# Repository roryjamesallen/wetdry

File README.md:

# wetdry
Wet/Dry control for Eurorack

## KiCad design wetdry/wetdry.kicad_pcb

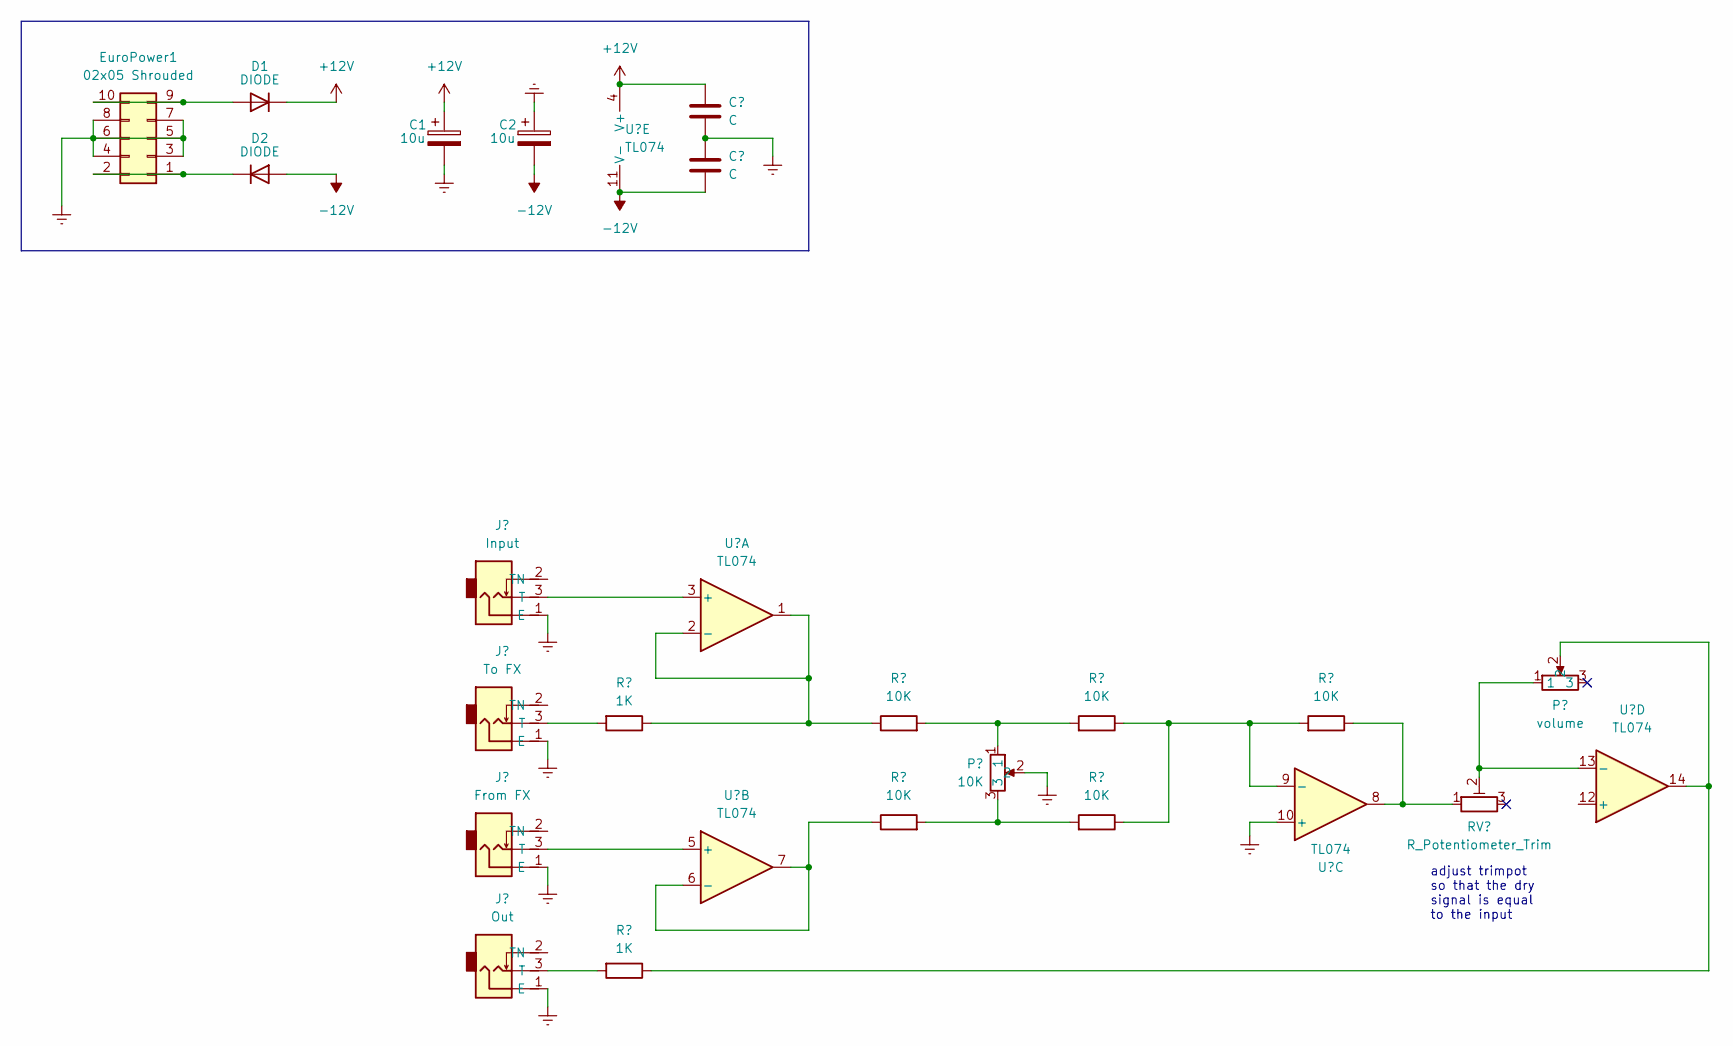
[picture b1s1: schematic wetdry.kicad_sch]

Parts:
C1, C2: 10u; CP_Radial_D5.0mm_P2.50mm
D1, D2: DIODE; D_DO-41_SOD81_P7.62mm_Horizontal
EuroPower1: 02x05 Shrouded; Eurorack Power Header

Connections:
+12V: C1.1, D1.2 (K)
-12V: C2.2, D2.1 (A)
Earth: C1.2, C2.1, EuroPower1.3, EuroPower1.4, EuroPower1.5, EuroPower1.6, EuroPower1.7, EuroPower1.8
unnamed: D1.1 (A), EuroPower1.9, EuroPower1.10
unnamed: D2.2 (K), EuroPower1.1, EuroPower1.2

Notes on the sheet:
adjust trimpot so that the dry signal is equal to the input

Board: 2 copper layers, 5 parts (0 on the bottom side), 5 nets, no tracks yet.

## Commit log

2022-05-02 Create KiCad
